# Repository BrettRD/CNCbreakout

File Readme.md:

# CNCbreakout

This is the working folder for the breakout board to wire the FPGA interface cards into the CNC cabinet.

The interfaces as described did not standardise voltages on the limit switches and left some signal poalrities up to chance

This board also has LED outputs showing the current state of all limits and home switches.

## PCB
There is a toner-transfer PCB in the compactus, but it requires about six hours of work fitting track jumpers.

The KiCad PCB simply has these as top-layer tracks. Export gerbers and buy PCBs; save your sanity.

## Documents:
There is no manual for the 220V X-axis servo controller. This repo contains the closest approximation, and seems to have the same menu and pinouts.

The pinouts for the interface cables currently only exist within the KiCad document.  Some of these will need to have piggyback connections.  With a bit of work and sanity checking, these pinouts can be converted to tables or PDF diagrams.

## Current Hardware:
The inactive X-axis motor has a fault in its signal lines pinout. This can be seen on the servo controller: navigate the menu to a live encoder display.  See the maxsineMotorpinout spreadsheet for the correct wiring.

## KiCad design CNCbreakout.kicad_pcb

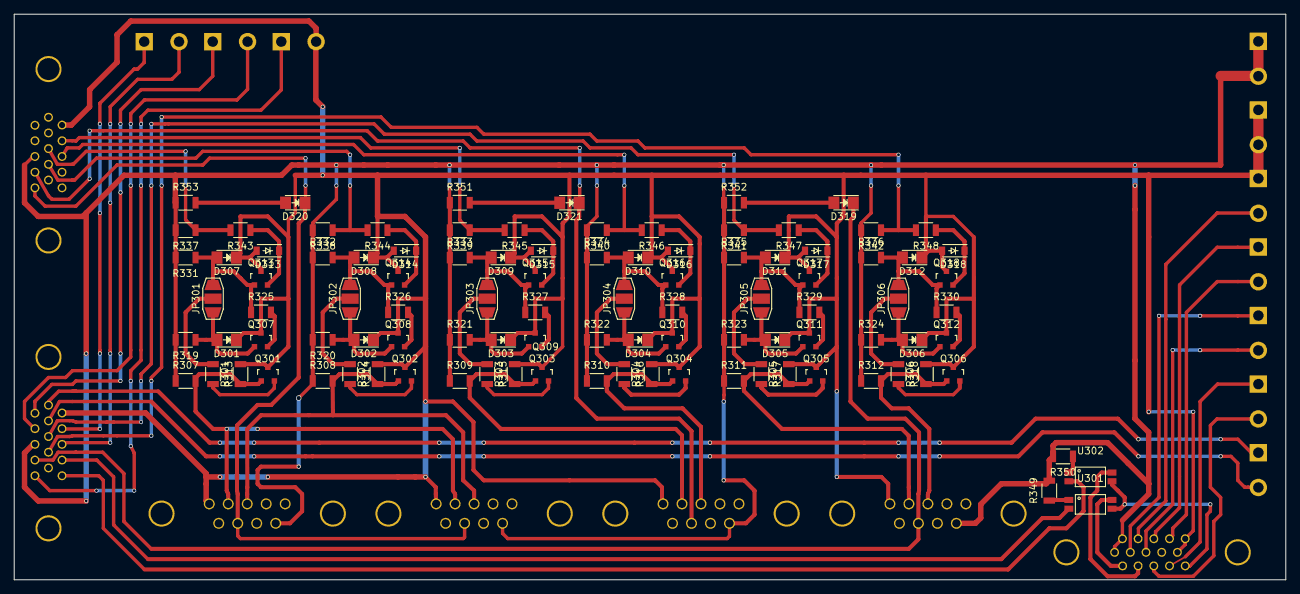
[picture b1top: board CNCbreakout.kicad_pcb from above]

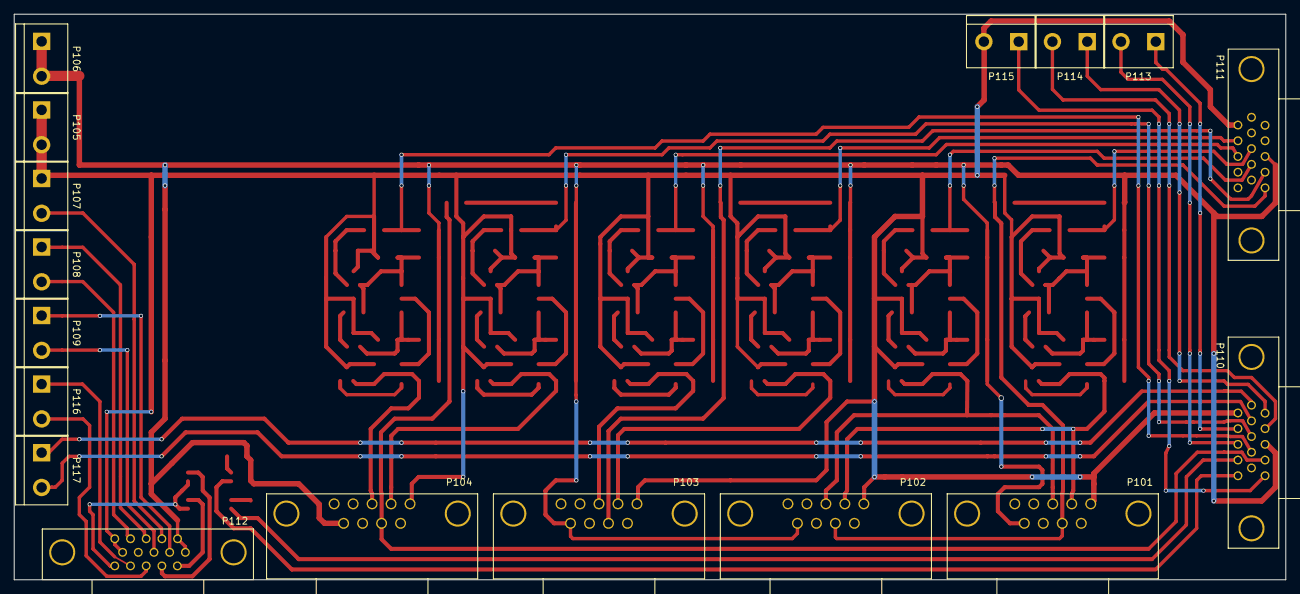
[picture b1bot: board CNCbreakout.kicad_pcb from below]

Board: 2 copper layers, 185.5 x 82.5 mm, 117 parts (17 on the bottom side), 77 nets.

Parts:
D301, D302, D303, D304, D305, D306, D307, D308, D309, D310, D311, D312, D319, D320, D321: LED; LED_1206
D313, D314, D315, D316, D317, D318: ZENERsmall; SOD-123
JP301, JP302, JP303, JP304, JP305, JP306: JUMPER3; JumperDouble
P101: X1; DE9FC
P102: X2; DE9FC
P103: Y; DE9FC
P104: Z; DE9FC
P105: GND; bornier2
P106: +24V; bornier2
P107: VFD_Stop; bornier2
P108: VFD_FwdRev; bornier2
P109: VFD_Aux; bornier2
P110: Z_STOP; DE15HDFC
P111: XY_STOP; DE15HDFC
P112: VFD_IN; DE15HDFC
P113: Zaux1; bornier2
P114: Zaux2; bornier2
P115: Zaux3; bornier2
P116: VFD_Speed; bornier2
P117: VFD_Temp; bornier2
Q301, Q302, Q303, Q304, Q305, Q306, Q307, Q308, Q309, Q310, Q311, Q312, Q313, Q314, Q315, Q316, Q317, Q318: Q_NPN_CBE; SOT-23
R301, R302, R303, R304, R305, R306, R319, R320, R321, R322, R323, R324, R331, R332, R333, R334, R335, R336, R339, R340, R341, R342: 5K; R_1206
R307, R308, R309, R310, R311, R312: 20K; R_1206
R313, R314, R315, R316, R317, R318, R325, R326, R327, R328, R329, R330, R337, R338, R343, R344, R345, R346, R347, R348, R349, R350, R351, R352, R353: 10K; R_1206
U301, U302: TCMT1108

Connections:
+24V: P101.9, P102.9, P103.9, P104.9, P106.1, P106.2, P110.13, P111.13, P112.1, P112.6, R307.1, R308.1, R309.1, R310.1, R311.1, R312.1, R319.2, R320.2, R321.1, R322.1, R323.1, R324.1, R331.2, R332.1, R333.1, R334.1, R335.1, R336.1, R337.2, R338.2, R339.2, R340.2, R341.2, R342.2, R349.2, R350.2, R351.1, R352.1, R353.1
DGND: P112.15, U301.3, U302.3
DIn_1: P107.2, P112.2
DIn_2: P109.1, P112.7
DIn_3: P108.1, P112.3
DIn_5: P109.2, P112.8
DIn_6: P108.2, P112.4
DOut_1: P112.11, U301.4
DOut_2: P112.12, U302.4
F1_LIM: P101.2, P102.2, Q301.1, R301.1, R307.2
GND: D301.1, D302.1, D303.1, D304.1, D305.1, D306.1, D307.1, D308.1, D309.1, D310.1, D311.1, D312.1, D313.2, D314.2, D315.2, D316.2, D317.2, D318.2, P101.1, P102.1, P103.1, P104.1, P105.1, P105.2, P107.1, P110.1, P111.1, P112.5, P112.10, P115.2, Q301.3, Q302.3, Q303.3, Q304.3, Q305.3, Q306.3, Q307.3, Q308.3, Q309.3, Q310.3, Q311.3, Q312.3, Q313.3, Q314.3, Q315.3, Q316.3, Q317.3, Q318.3, R301.2, R302.2, R303.2, R304.2, R305.2, R306.2
HomeX: D320.1, P101.7, P102.7, P111.15
HomeY: D321.1, P103.7, P111.14
HomeZ: D319.1, P104.7, P110.14
LimX+: P111.8, R337.1, R343.2
LimX-: P111.9, R338.1, R344.2
LimY+: P111.2, R339.1, R345.2
LimY-: P111.3, R340.1, R346.2
LimZ+: P110.8, R341.1, R347.2
LimZ-: P110.9, R342.1, R348.2
LoopA: P112.13, P116.2
LoopB: P112.14, P116.1
unnamed: D301.2, JP301.3, Q307.1, R319.1
unnamed: D302.2, JP302.3, Q308.1, R320.1
unnamed: D303.2, JP303.3, Q309.1, R321.2
unnamed: D304.2, JP304.3, Q310.1, R322.2
unnamed: D305.2, JP305.3, Q311.1, R323.2
unnamed: D306.2, JP306.3, Q312.1, R324.2
unnamed: D307.2, JP301.1, Q313.1, R325.1, R331.1
unnamed: D308.2, JP302.1, Q314.1, R326.1, R332.2
unnamed: D309.2, JP303.1, Q315.1, R327.1, R333.2
unnamed: D310.2, JP304.1, Q316.1, R328.1, R334.2
unnamed: D311.2, JP305.1, Q317.1, R329.1, R335.2
unnamed: D312.2, JP306.1, Q318.1, R330.1, R336.2
unnamed: D313.1, Q313.2, R343.1
unnamed: D314.1, Q314.2, R344.1
unnamed: D315.1, Q315.2, R345.1
unnamed: D316.1, Q316.2, R346.1
unnamed: D317.1, Q317.2, R347.1
unnamed: D318.1, Q318.2, R348.1
unnamed: D319.2, R352.2
unnamed: D320.2, R353.2
unnamed: D321.2, R351.2
unnamed: JP301.2, R313.1
unnamed: JP302.2, R314.1
unnamed: JP303.2, R315.1
unnamed: JP304.2, R316.1
unnamed: JP305.2, R317.1
unnamed: JP306.2, R318.1
unnamed: P110.11, P114.1
unnamed: P110.12, P114.2
unnamed: P110.15, P115.1
unnamed: Q301.2, R313.2
unnamed: Q302.2, R314.2
unnamed: Q303.2, R315.2
unnamed: Q304.2, R316.2
unnamed: Q305.2, R317.2
unnamed: Q306.2, R318.2
unnamed: Q307.2, R325.2
unnamed: Q308.2, R326.2
unnamed: Q309.2, R327.2
unnamed: Q310.2, R328.2
unnamed: Q311.2, R329.2
unnamed: Q312.2, R330.2
unnamed: R349.1, U301.1
unnamed: R350.1, U302.1
R1_LIM: P101.3, P102.3, Q302.1, R302.1, R308.2
SOL1: P110.2, P113.1
SOL2: P110.3, P113.2
SpindleHallA: P110.4, U301.2
SpindleHallB: P110.5, U302.2
SpindleTherm+: P110.7, P117.2
SpindleTherm-: P110.6, P117.1
Y+Lim: P103.2, Q303.1, R303.1, R309.2
Y-Lim: P103.3, Q304.1, R304.1, R310.2
Z+Lim: P104.2, Q305.1, R305.1, R311.2
Z-Lim: P104.3, Q306.1, R306.1, R312.2

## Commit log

2016-07-12 Most pinouts done
2016-07-15 added spindle hall, assignd footprints
2016-07-22 cleanup and added enable intercept
2016-08-18 started pcb layout
2016-08-22 added opto and DE footprints
2016-09-19 set limits to pull down, optional invert
2016-09-22 closer to full routing
2016-10-10 adjusted DE15 footprint, added aux Z-stage lines
2016-10-10 added thermistor
2016-10-10 full route
2016-10-24 added enable input connector
2016-11-09 checked limits and homes, removed enable, adjusted routing
2016-11-14 added pdf of copper layers
2016-11-14 added toner transfer files
2017-03-02 added documents and a readme
2017-03-02 Tweaked readme
2017-08-17 exported PDFs of the schematics
